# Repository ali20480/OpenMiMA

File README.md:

# OpenMiMA

This repository contains the supplementary material of the paper "OpenMiMA: An Open-Source Memristor Interfacing and Compute Board for Neuromorphic Edge-AI Applications" by Ali Safa et al., College of Science and Engineering, Hamad Bin Khalifa University, Doha, Qatar.

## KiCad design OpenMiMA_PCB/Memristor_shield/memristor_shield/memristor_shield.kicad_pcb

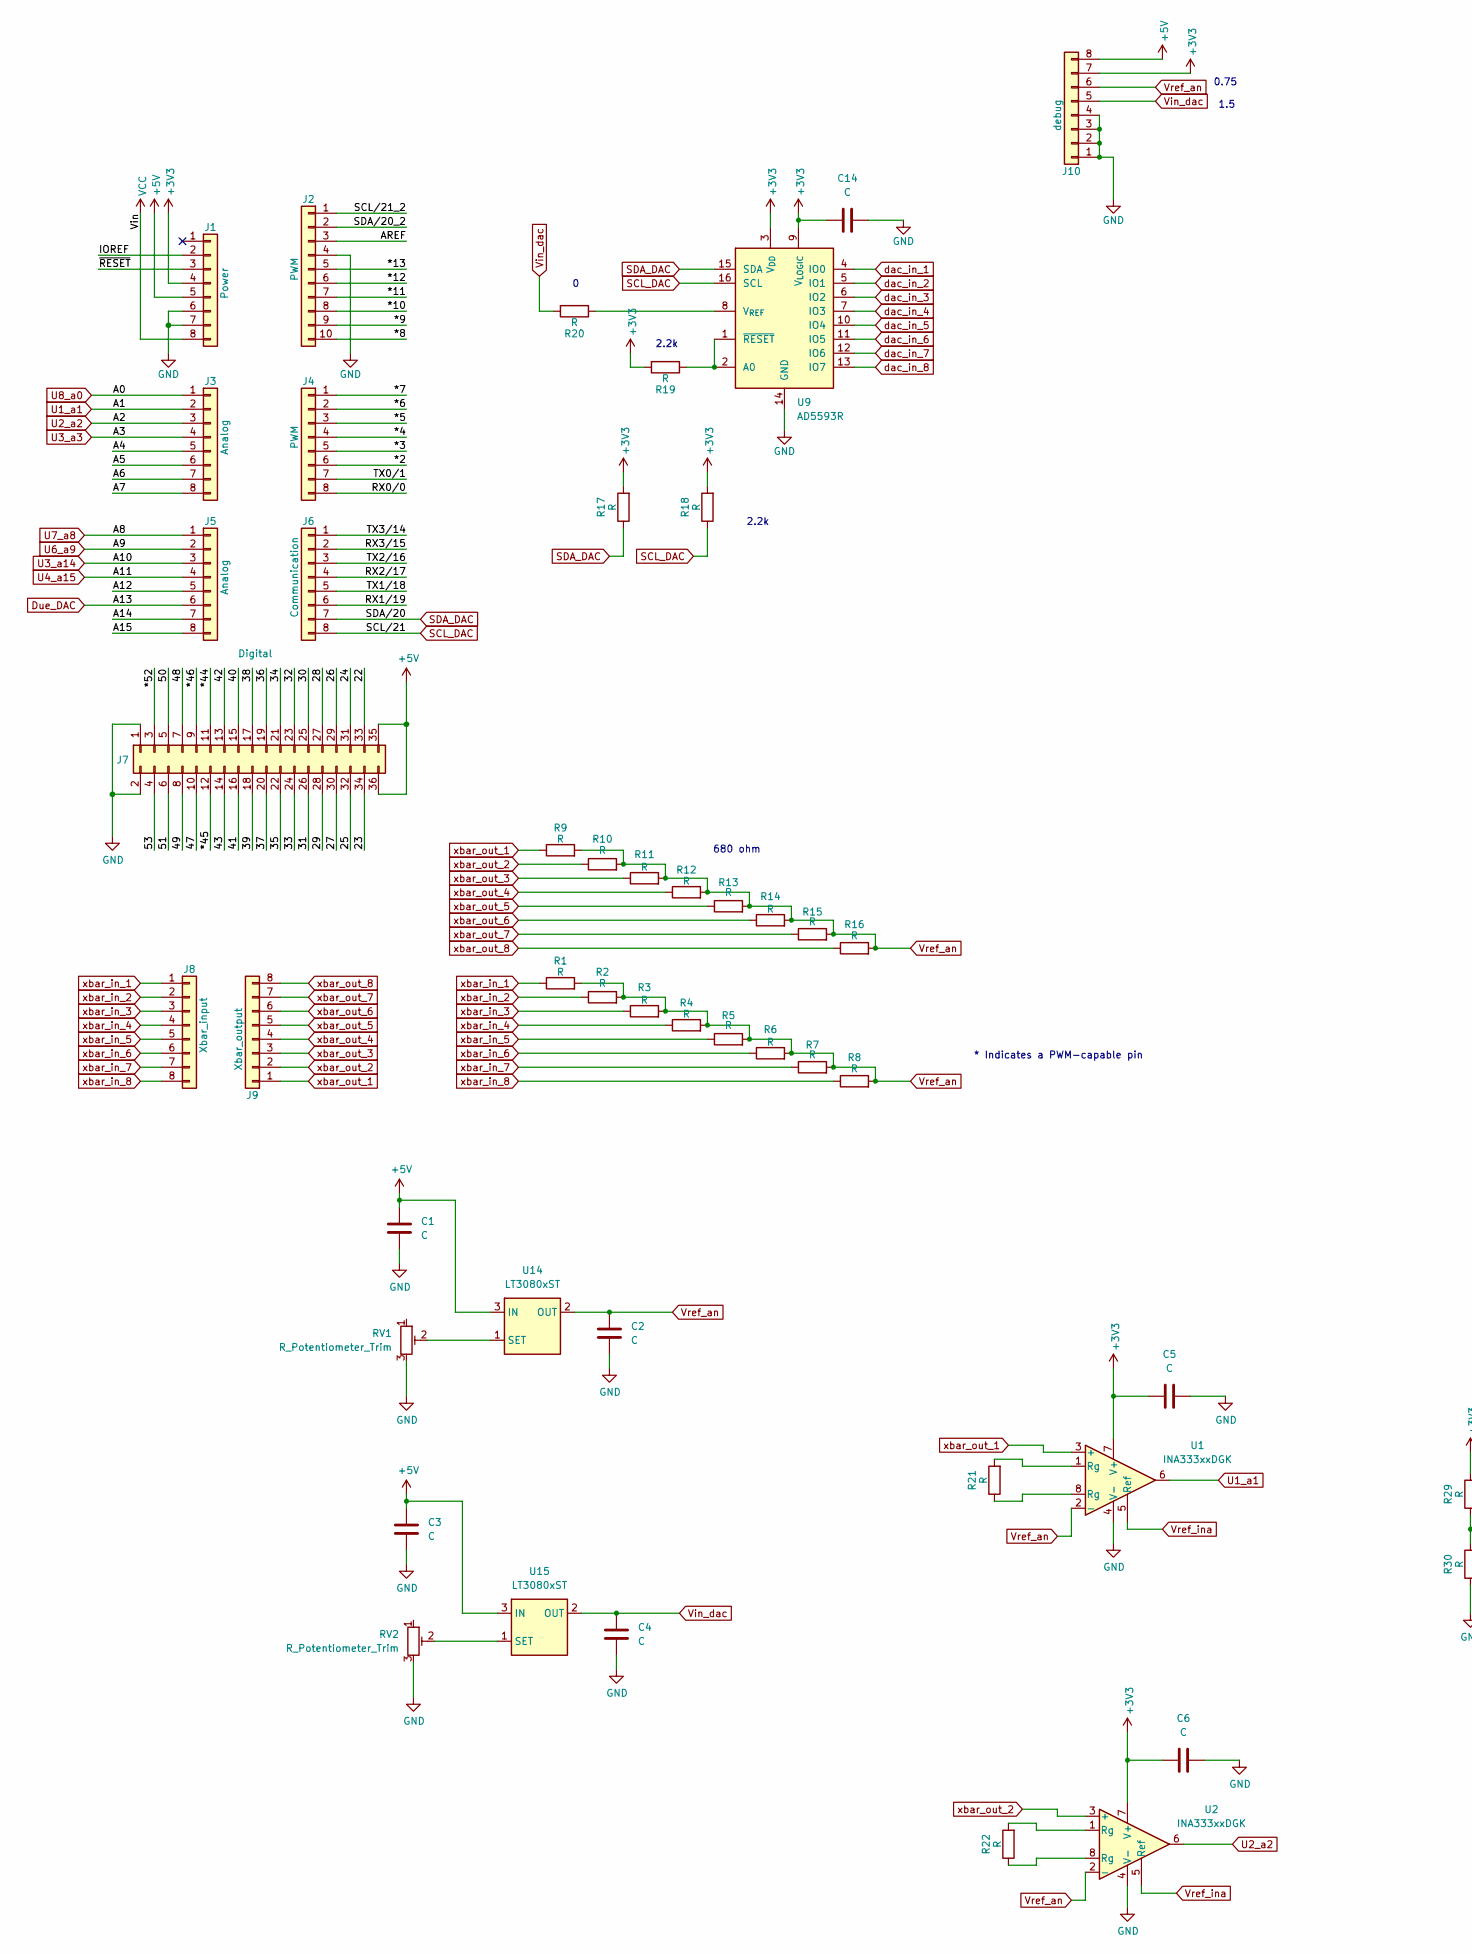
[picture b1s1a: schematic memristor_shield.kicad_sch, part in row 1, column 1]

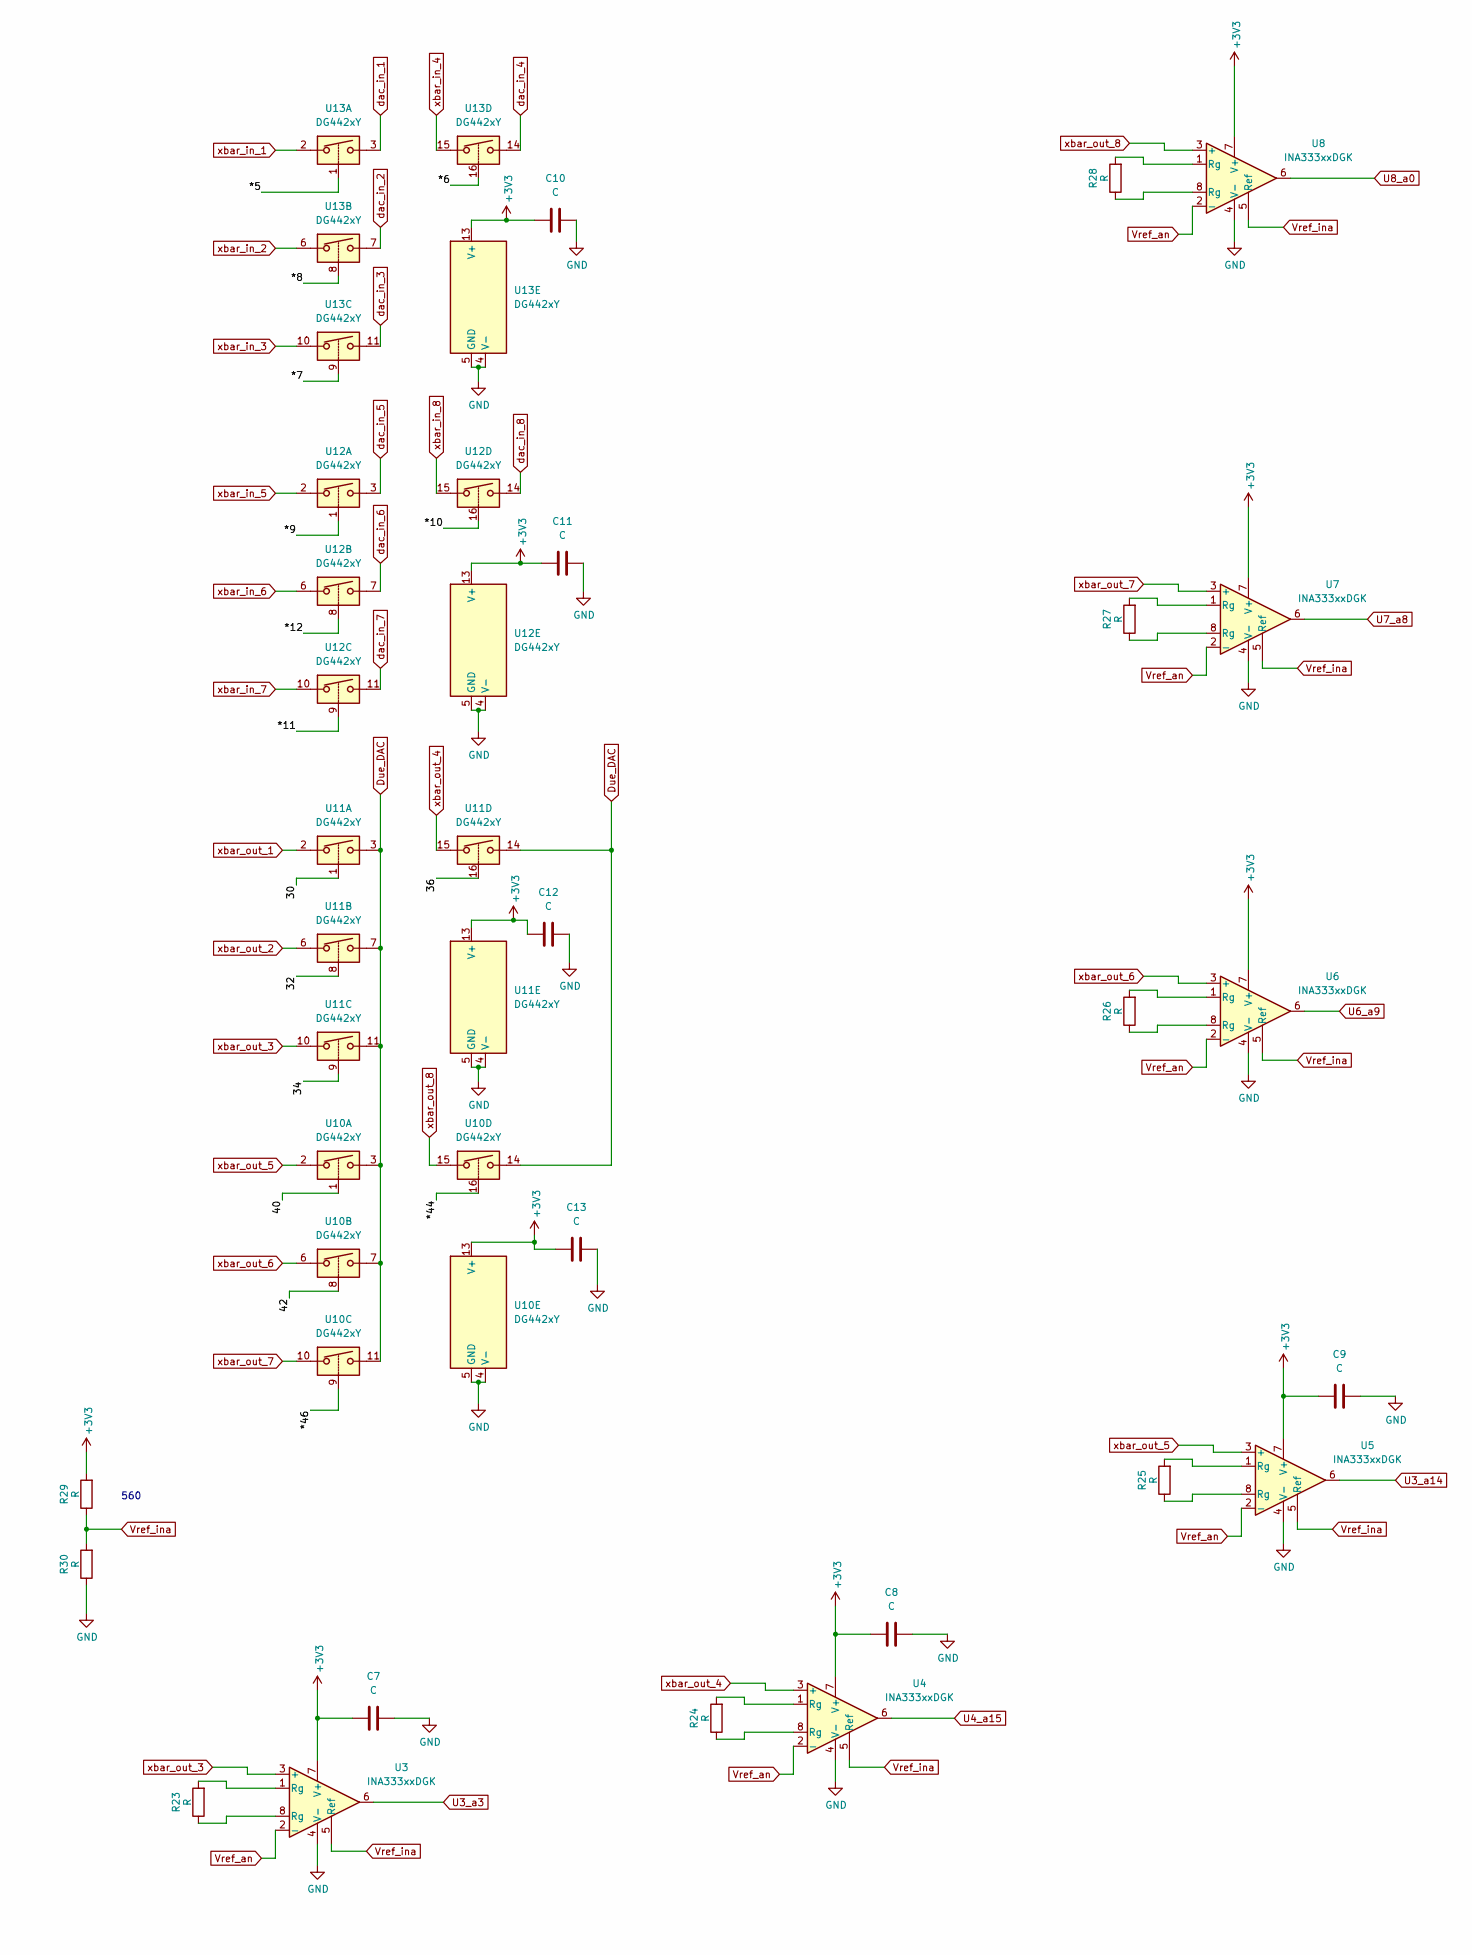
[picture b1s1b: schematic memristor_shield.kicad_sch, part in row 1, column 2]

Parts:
C1, C2, C3, C4, C5, C6, C7, C8, C9, C10, C11, C12, C13, C14: C; C_0805_2012Metric_Pad1.18x1.45mm_HandSolder
J1: Power; PinSocket_1x08_P2.54mm_Vertical
J2: PWM; PinSocket_1x10_P2.54mm_Vertical
J3, J5: Analog; PinSocket_1x08_P2.54mm_Vertical
J4: PWM; PinSocket_1x08_P2.54mm_Vertical
J6: Communication; PinSocket_1x08_P2.54mm_Vertical
J7: Digital; PinSocket_2x18_P2.54mm_Vertical
J8: Xbar_input; PinSocket_1x08_P2.54mm_Vertical
J9: Xbar_output; PinSocket_1x08_P2.54mm_Vertical
J10: debug; PinSocket_1x08_P2.54mm_Vertical
R1, R2, R3, R4, R5, R6, R7, R8, R9, R10, R11, R12, R13, R14, R15, R16, R17, R18, R19, R20, R21, R22, R23, R24, R25, R26, R27, R28, R29, R30: R; R_0805_2012Metric_Pad1.20x1.40mm_HandSolder
RV1, RV2: R_Potentiometer_Trim; Potentiometer_Bourns_3296W_Vertical
U1, U2, U3, U4, U5, U6, U7, U8: INA333xxDGK; VSSOP-8_3x3mm_P0.65mm
U9: AD5593R; TSSOP-16_4.4x5mm_P0.65mm
U10, U11, U12, U13: DG442xY; SOIC-16_3.9x9.9mm_P1.27mm
U14, U15: LT3080xST; SOT-223

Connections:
+3V3: C5.1, C6.1, C7.1, C8.1, C9.1, C10.1, C11.1, C12.1, C13.1, C14.1, J1.4, J10.7, R17.2, R18.2, R19.2, R29.2, U1.7 (V+), U2.7 (V+), U3.7 (V+), U4.7 (V+), U5.7 (V+), U6.7 (V+), U7.7 (V+), U8.7 (V+), U9.3 (V_{DD}), U9.9 (V_{LOGIC}), U10.13 (V+), U11.13 (V+), U12.13 (V+), U13.13 (V+)
+5V: C1.1, C3.1, J1.5, J7.35, J7.36, J10.8, U14.3 (IN), U15.3 (IN)
/22: J7.33
/23: J7.34
/24: J7.31
/25: J7.32
/26: J7.29
/27: J7.30
/28: J7.27
/29: J7.28
/30: J7.25, U11.1
/31: J7.26
/32: J7.23, U11.8
/33: J7.24
/34: J7.21, U11.9
/35: J7.22
/36: J7.19, U11.16
/37: J7.20
/38: J7.17
/39: J7.18
/40: J7.15, U10.1
/41: J7.16
/42: J7.13, U10.8
/43: J7.14
/47: J7.10
/48: J7.7
/49: J7.8
/50: J7.5
/51: J7.6
/53: J7.4
/*2: J4.6
/*3: J4.5
/*4: J4.4
/*5: J4.3, U13.1
/*6: J4.2, U13.16
/*7: J4.1, U13.9
/*8: J2.10, U13.8
/*9: J2.9, U12.1
/*10: J2.8, U12.16
/*11: J2.7, U12.9
/*12: J2.6, U12.8
/*13: J2.5
/*44: J7.11, U10.16
/*45: J7.12
/*46: J7.9, U10.9
/*52: J7.3
/A4: J3.5
/A5: J3.6
/A6: J3.7
/A7: J3.8
/A12: J5.5
/A14: J5.7
/A15: J5.8
/AREF: J2.3
/IOREF: J1.2
/RX0/0: J4.8
/RX1/19: J6.6
/RX2/17: J6.4
/RX3/15: J6.2
/SCL/21_2: J2.1
/SDA/20_2: J2.2
/TX0/1: J4.7
/TX1/18: J6.5
/TX2/16: J6.3
/TX3/14: J6.1
/~RESET: J1.3
Due_DAC: J5.6, U10.3, U10.7, U10.11, U10.14, U11.3, U11.7, U11.11, U11.14
GND: C1.2, C2.2, C3.2, C4.2, C5.2, C6.2, C7.2, C8.2, C9.2, C10.2, C11.2, C12.2, C13.2, C14.2, J1.6, J1.7, J2.4, J7.1, J7.2, J10.1, J10.2, J10.3, J10.4, R30.1, RV1.3, RV2.3, U1.4 (V-), U2.4 (V-), U3.4 (V-), U4.4 (V-), U5.4 (V-), U6.4 (V-), U7.4 (V-), U8.4 (V-), U9.14 (GND), U10.4 (V-), U10.5 (GND), U11.4 (V-), U11.5 (GND), U12.4 (V-), U12.5 (GND), U13.4 (V-), U13.5 (GND)
unnamed: R21.1, U1.8 (Rg)
unnamed: R21.2, U1.1 (Rg)
unnamed: R22.1, U2.8 (Rg)
unnamed: R22.2, U2.1 (Rg)
unnamed: R23.1, U3.8 (Rg)
unnamed: R23.2, U3.1 (Rg)
unnamed: R24.1, U4.8 (Rg)
unnamed: R24.2, U4.1 (Rg)
unnamed: R25.1, U5.8 (Rg)
unnamed: R25.2, U5.1 (Rg)
unnamed: R26.1, U6.8 (Rg)
unnamed: R26.2, U6.1 (Rg)
unnamed: R27.1, U7.8 (Rg)
unnamed: R27.2, U7.1 (Rg)
unnamed: R28.1, U8.8 (Rg)
unnamed: R28.2, U8.1 (Rg)
unnamed: R19.1, U9.1 (~RESET), U9.2 (A0)
unnamed: R20.1, U9.8 (V_{REF})
unnamed: RV1.2, U14.1 (SET)
unnamed: RV2.2, U15.1 (SET)
SCL_DAC: J6.8, R18.1, U9.16 (SCL)
SDA_DAC: J6.7, R17.1, U9.15 (SDA)
U1_a1: J3.2, U1.6
U2_a2: J3.3, U2.6
U3_a3: J3.4, U3.6
U3_a14: J5.3, U5.6
U4_a15: J5.4, U4.6
U6_a9: J5.2, U6.6
U7_a8: J5.1, U7.6
U8_a0: J3.1, U8.6
VCC: J1.8
Vin_dac: C4.1, J10.5, R20.2, U15.2 (OUT), U15.4 (OUT)
Vref_an: C2.1, J10.6, R1.2, R2.2, R3.2, R4.2, R5.2, R6.2, R7.2, R8.2, R9.2, R10.2, R11.2, R12.2, R13.2, R14.2, R15.2, R16.2, U1.2 (-), U2.2 (-), U3.2 (-), U4.2 (-), U5.2 (-), U6.2 (-), U7.2 (-), U8.2 (-), U14.2 (OUT), U14.4 (OUT)
Vref_ina: R29.1, R30.2, U1.5 (Ref), U2.5 (Ref), U3.5 (Ref), U4.5 (Ref), U5.5 (Ref), U6.5 (Ref), U7.5 (Ref), U8.5 (Ref)
dac_in_1: U9.4 (IO0), U13.3
dac_in_2: U9.5 (IO1), U13.7
dac_in_3: U9.6 (IO2), U13.11
dac_in_4: U9.7 (IO3), U13.14
dac_in_5: U9.10 (IO4), U12.3
dac_in_6: U9.11 (IO5), U12.7
dac_in_7: U9.12 (IO6), U12.11
dac_in_8: U9.13 (IO7), U12.14
xbar_in_1: J8.1, R1.1, U13.2
xbar_in_2: J8.2, R2.1, U13.6
xbar_in_3: J8.3, R3.1, U13.10
xbar_in_4: J8.4, R4.1, U13.15
xbar_in_5: J8.5, R5.1, U12.2
xbar_in_6: J8.6, R6.1, U12.6
xbar_in_7: J8.7, R7.1, U12.10
xbar_in_8: J8.8, R8.1, U12.15
xbar_out_1: J9.1, R9.1, U1.3 (+), U11.2
xbar_out_2: J9.2, R10.1, U2.3 (+), U11.6
xbar_out_3: J9.3, R11.1, U3.3 (+), U11.10
xbar_out_4: J9.4, R12.1, U4.3 (+), U11.15
xbar_out_5: J9.5, R13.1, U5.3 (+), U10.2
xbar_out_6: J9.6, R14.1, U6.3 (+), U10.6
xbar_out_7: J9.7, R15.1, U7.3 (+), U10.10
xbar_out_8: J9.8, R16.1, U8.3 (+), U10.15

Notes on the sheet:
680 ohm
560
2.2k
1.5
0.75
* Indicates a PWM-capable pin

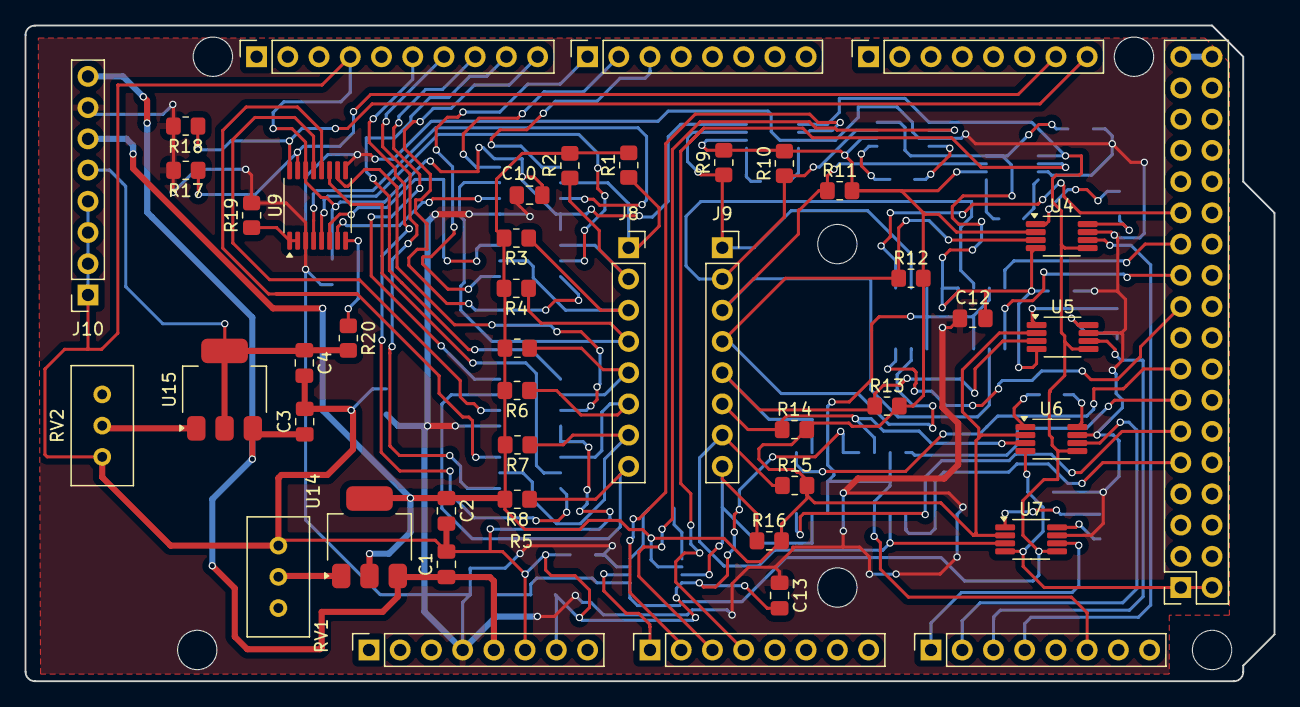
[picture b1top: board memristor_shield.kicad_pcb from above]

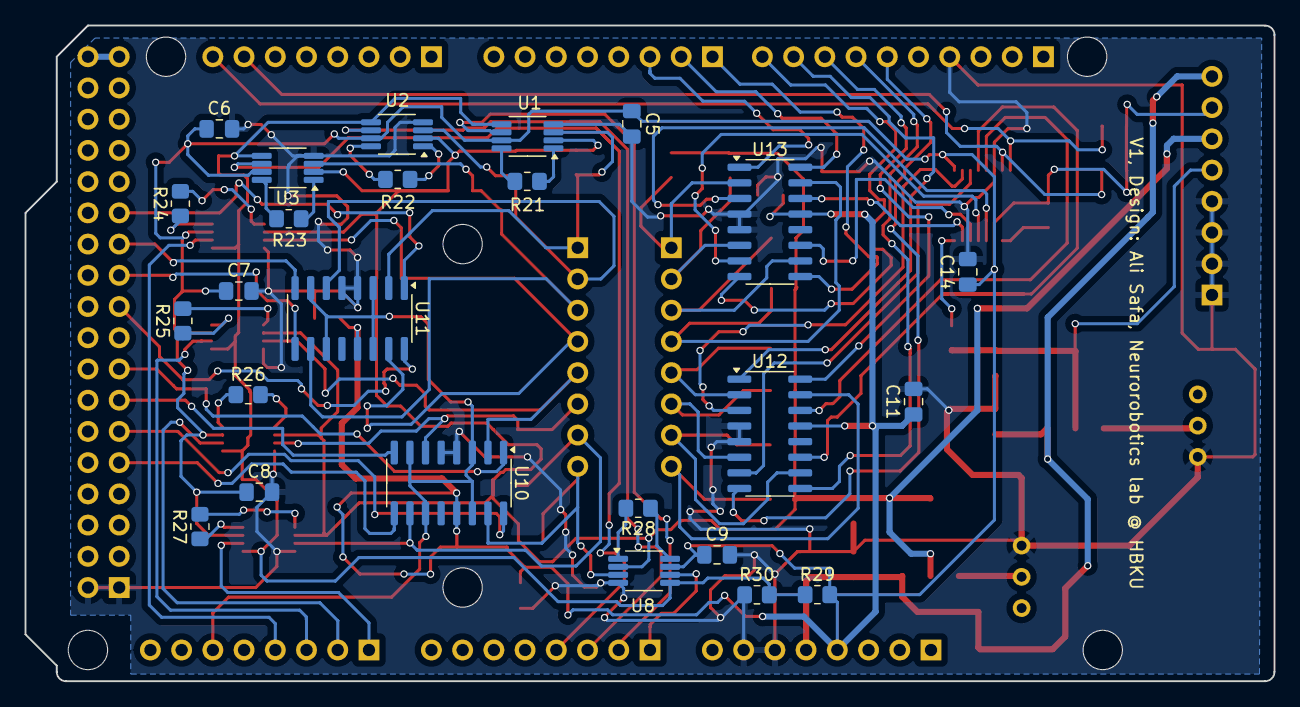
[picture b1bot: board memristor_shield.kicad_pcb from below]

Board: 2 copper layers, 101.6 x 53.3 mm, 77 parts (25 on the bottom side), 77 nets.

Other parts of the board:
MH1, MH2, MH3, MH4, MH5, MH6: MountingHole_3.2mm
